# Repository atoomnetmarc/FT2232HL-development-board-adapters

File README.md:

# FT2232HL development board to iceprog

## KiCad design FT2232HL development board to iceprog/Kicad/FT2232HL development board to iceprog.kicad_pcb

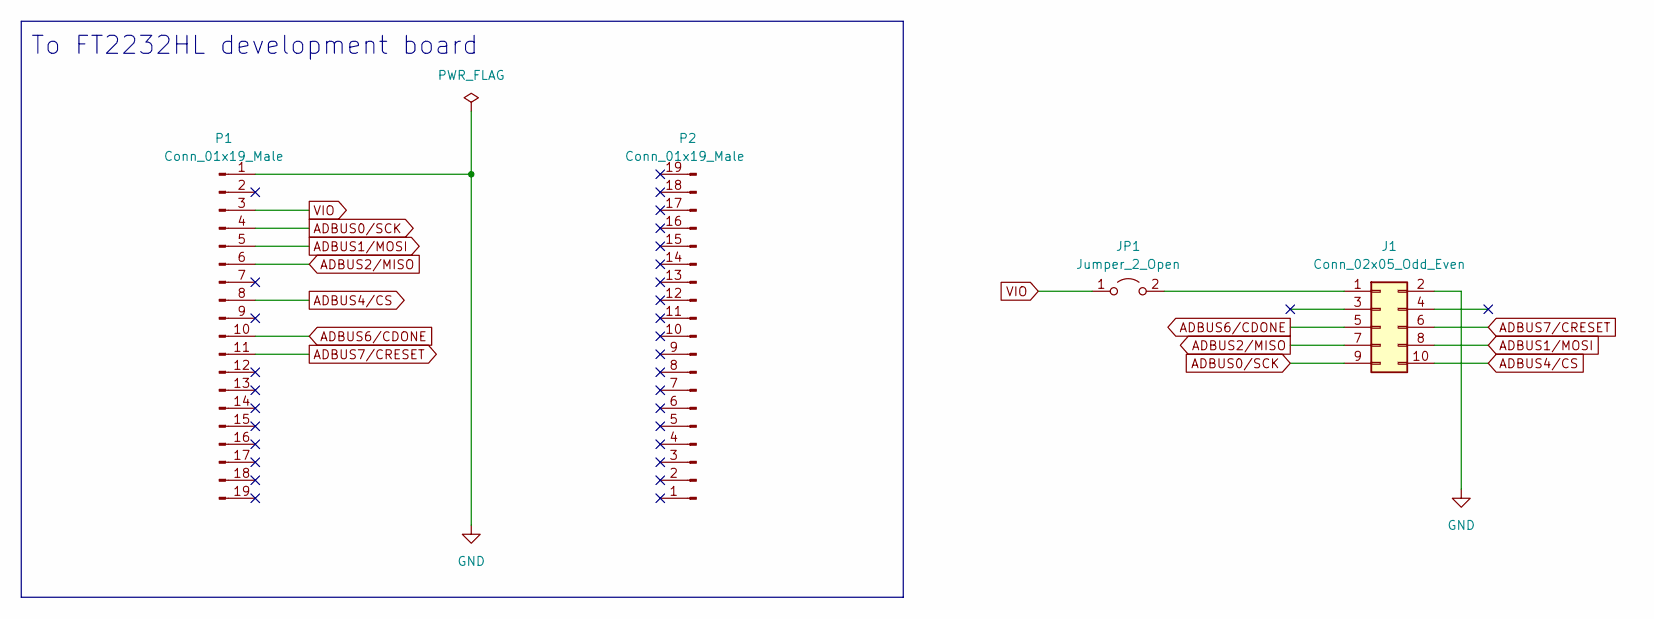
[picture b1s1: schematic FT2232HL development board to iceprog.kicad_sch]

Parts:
J1: Conn_02x05_Odd_Even; IDC-Header_2x05_P2.54mm_Horizontal
JP1: Jumper_2_Open; PinHeader_1x02_P2.54mm_Vertical
P1, P2: Conn_01x19_Male; PinHeader_1x19_P2.54mm_Vertical

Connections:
ADBUS0/SCK: J1.9, P1.4
ADBUS1/MOSI: J1.8, P1.5
ADBUS2/MISO: J1.7, P1.6
ADBUS4/CS: J1.10, P1.8
ADBUS6/CDONE: J1.5, P1.10
ADBUS7/CRESET: J1.6, P1.11
GND: J1.2, P1.1
unnamed: J1.1, JP1.2 (B)
VIO: JP1.1 (A), P1.3

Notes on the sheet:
To FT2232HL development board

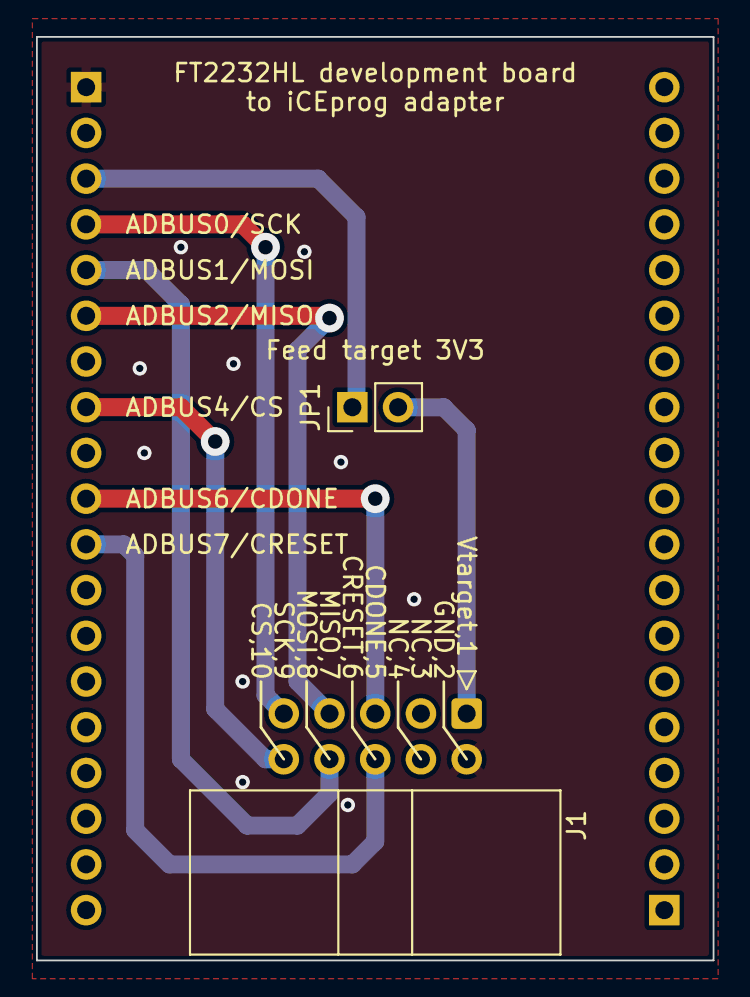
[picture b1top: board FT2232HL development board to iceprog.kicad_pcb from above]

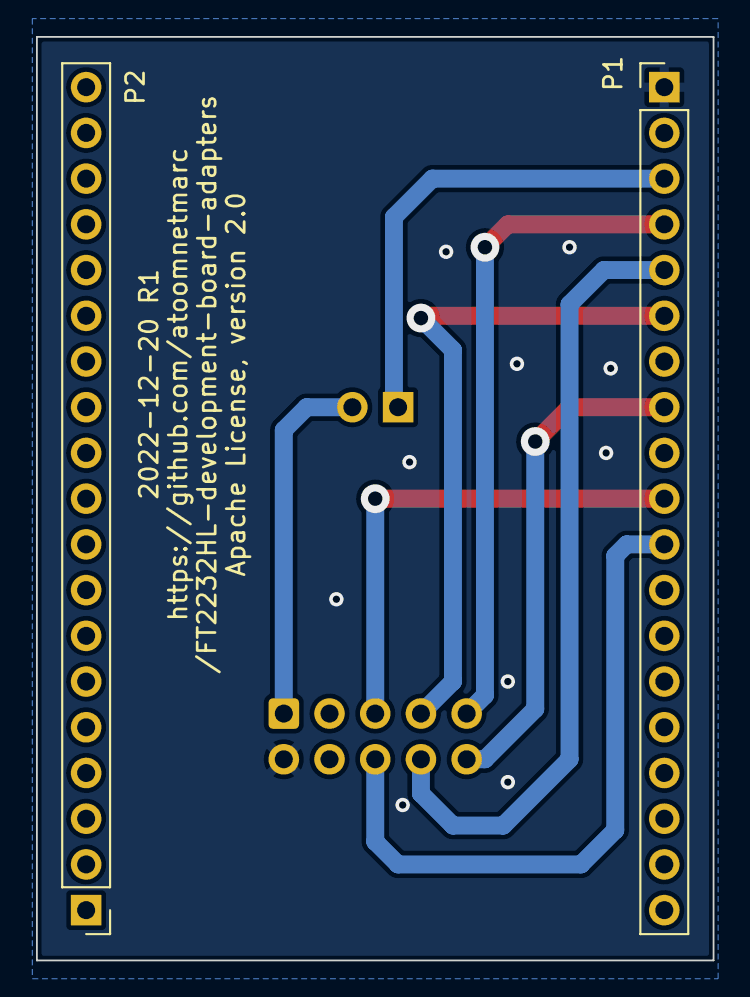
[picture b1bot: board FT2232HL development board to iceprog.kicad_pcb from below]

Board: 2 copper layers, 37.6 x 51.3 mm, 4 parts (2 on the bottom side), 9 nets.

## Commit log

2022-12-09 Swapped MOSI/MISO.

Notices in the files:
FT2232HL development board to iceprog/Kicad/FT2232HL development board to iceprog.kicad_pcb:
Apache License, version 2.0
README.md:
License: Apache 2.0
